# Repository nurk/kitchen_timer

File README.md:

### *Disclaimer*
*I am not a microcontroller developer nor am I a C-plusplus developer.  I am also definitively not a hardware designer.*

# Kitchen timer

A long time ago my lovely sister gave me a kitchen timer which would beep once when there are 10 minutes left and twice when there are 5 minutes left.  Unfortunately time got the better of the timer and it broke but I got hooked on those features.

I have been unable to find a replacement but after dabbling with some [circuits](https://github.com/nurk/8-bit-cpu) a bit I thought I might be able to make my own.

This repository contains the version(s) that I deem worthy of the internet.

You will find a software and hardware folder with each containing the respective versions.

The hardware folder contains a KiCad project where the symbols and footprints used have been added to a local library.  You will also find a pdf of the [schematic](https://github.com/nurk/kitchen_timer/blob/ce0c0dc44edd9d53a935f777b976885855d0056c/hardware/kitchen_timer_6.3/schematic.pdf), a screenshot of the [pcb](https://github.com/nurk/kitchen_timer/blob/ce0c0dc44edd9d53a935f777b976885855d0056c/hardware/kitchen_timer_6.3/pcb.png) and a screenshot of the [3D rendering](https://github.com/nurk/kitchen_timer/blob/ce0c0dc44edd9d53a935f777b976885855d0056c/hardware/kitchen_timer_6.3/3D.png).

The software folder contains an arduino ide project with the, well, software.

## User guide
I am not going to explain how to use a kitchen timer.  If the main function of the 4 buttons does not speak for themselves I did really bad.  I am only going to explain the extra features.

### Timer / C°
This switch toggles the display to show the timer and the measured temperature.

### Loud / Quiet
I bought cheap buzzers on amazon and they all seem a bit different.  Some are quiet and some are loud.  Because I was tired of changing the inline resistor for the buzzer I added a toggle to switch between two values.  One is louder, the other is quieter.

### Reset long press
Because you can fully turn off this device a way was needed to set the time for when you turn on the device.  The chance of you needing a timer of 0 minutes and 0 seconds is very slim.

After setting a time you can long press the **Reset** button until you hear a second beep and the set time will be stored.  When cycling the power the stored time will be loaded.

### Start/Stop long press
When you long press the **Start/Stop** button the letter `A` will appear and you will have entered the setup menu.  After releasing the **Start/Stop** button you will see `A5. 0`.  Clicking the **Start/Stop** button will cycle through the menu items:  
| Displayed        | Meaning         |
| :--------------: | :-------------: |
| `A5. 0`          | 5 minute alarm  |
| `A10.0`          | 10 minute alarm |
| `A15.0`          | 15 minute alarm |
| `A20.0`          | 20 minute alarm |
| `C 0.0`          | Temperature offset<sup>*</sup> |

<sup>*</sup> This was added in version 6.4.  It is a `C` because I cannot make a `T` with a 7-segment display.

For the alarms, the value after the `.` is the number of beeps that will sound when there are 'x' minutes left.  You can use the **Minutes** button to increase the number of beeps and the **Seconds** button to decrease the number of beeps.

To exit the setup menu just click the **Reset** button.

## Miscellaneous
Some component sizes might seem big for some.  Especially resistors and capacitors of size 0805.  Keep in mind I am hand soldering this and I am becoming an old fart with bad eyesight.

The microcontroller is an ATmega4808 which has way more flash storage than is needed.  I still chose this one because it is what I have and I am not going to buy a new variant for each project I do.

The battery charge controller I chose only charges at 500mA.  So you will need a battery with at least this capacity (or you have to change the resistor on the programming pin).  I have a 2000mA battery connected and I takes a fair while to charge.

**This is not a cost effective way to get a kitchen timer.  If you need one you are better of going to the store and buying one.**

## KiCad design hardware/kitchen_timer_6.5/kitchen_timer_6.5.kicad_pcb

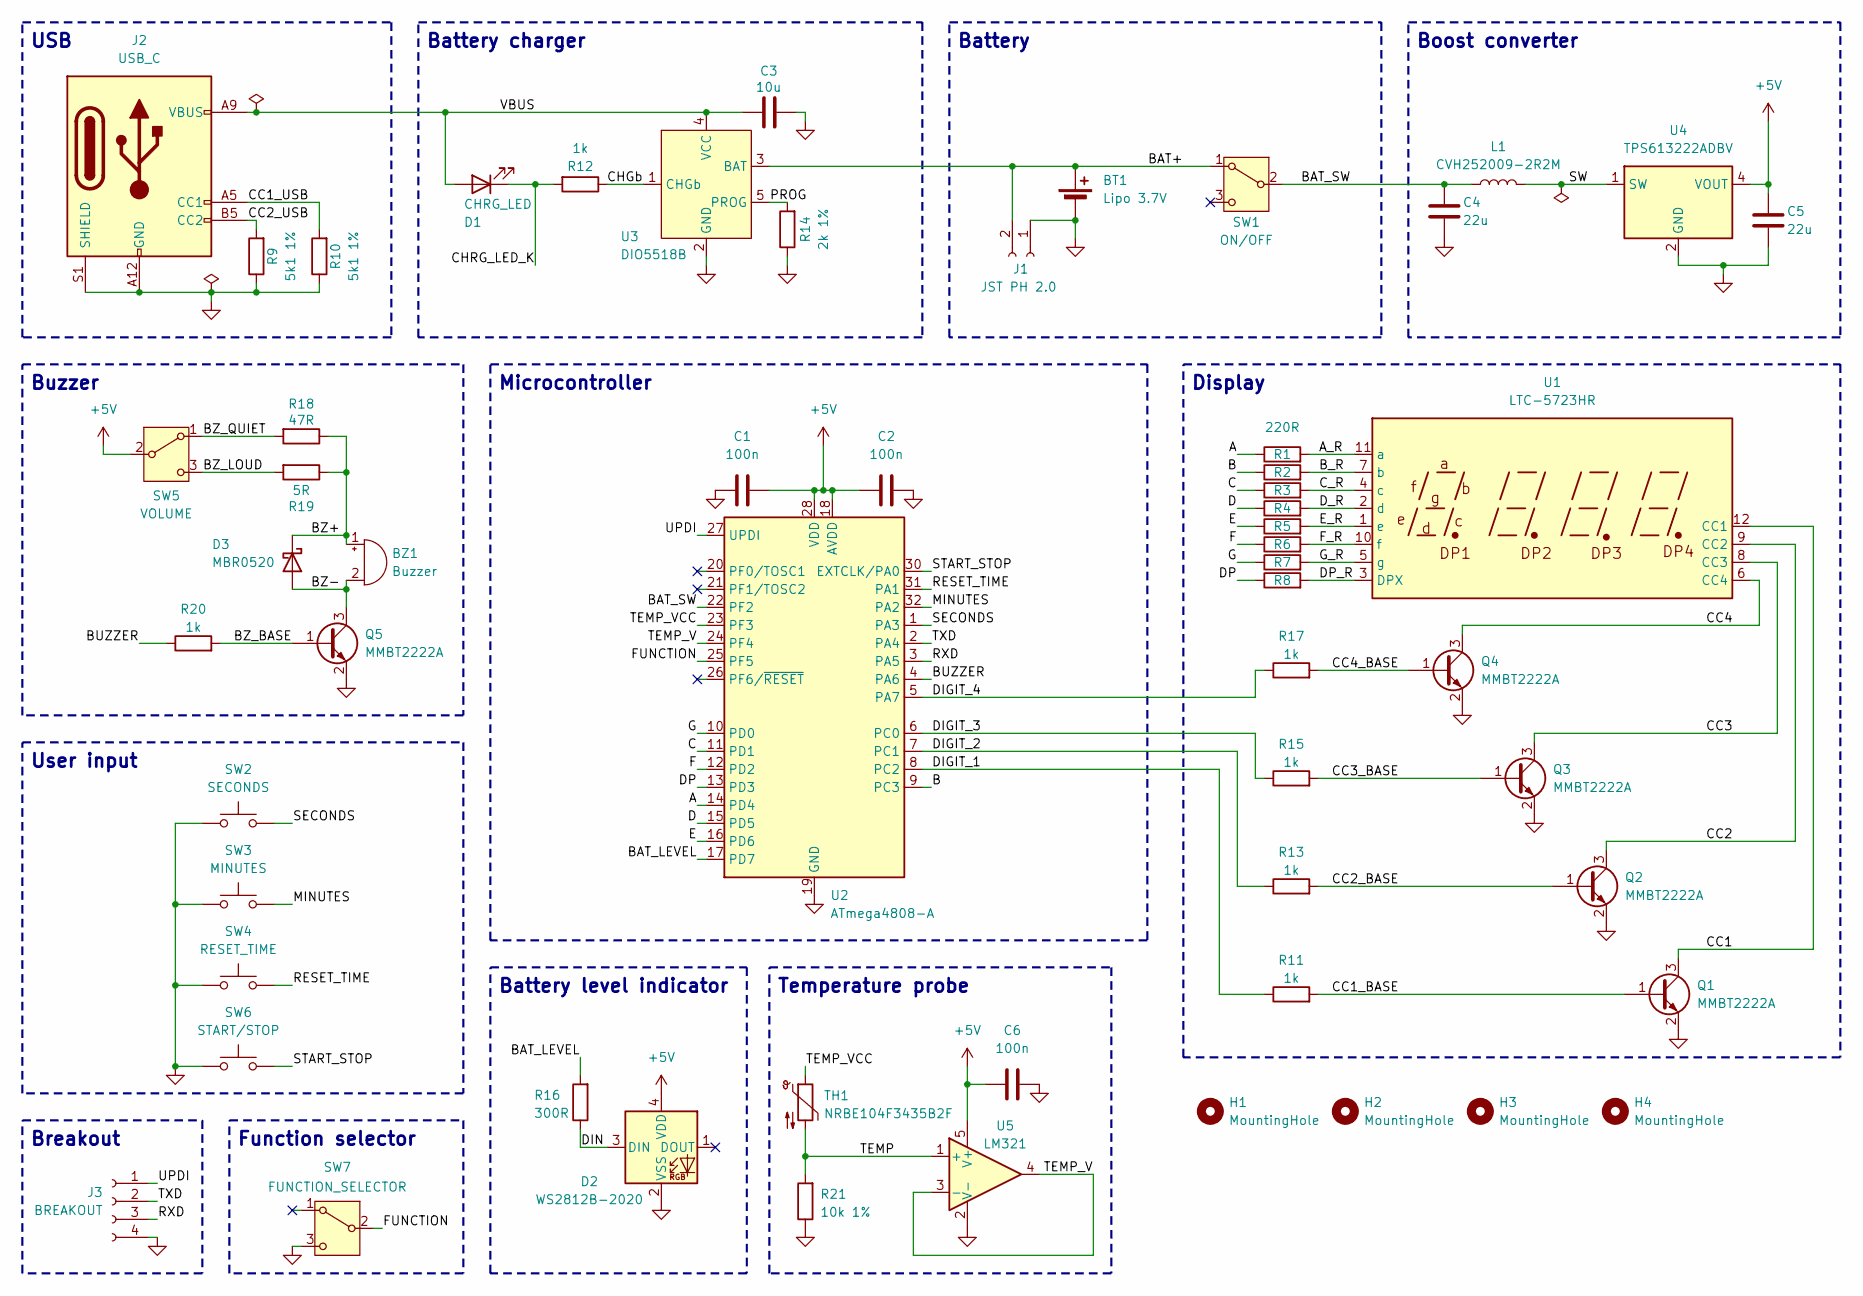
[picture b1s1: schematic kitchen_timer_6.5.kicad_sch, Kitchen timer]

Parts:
BT1: Lipo 3.7V
BZ1: Buzzer; MagneticBuzzer_ProSignal_ABT-410-RC
C1, C2, C6: 100n; C_0805_2012Metric_Pad1.18x1.45mm_HandSolder
C3: 10u; C_0805_2012Metric_Pad1.18x1.45mm_HandSolder
C4, C5: 22u; C_0805_2012Metric_Pad1.18x1.45mm_HandSolder
D1: CHRG_LED; D_0805_2012Metric_Pad1.15x1.40mm_HandSolder
D2: WS2812B-2020; LED_WS2812B-2020_2.0x2.0mm
D3: MBR0520; D_SOD-123
H1, H2, H3, H4: MountingHole; MountingHole_3.2mm_M3
J1: JST PH 2.0; JST_PH_S2B-PH-K_1x02_P2.00mm_Horizontal
J2: USB_C; USB_C_Receptacle_GCT_USB4125-xx-x-0190_6P_TopMnt_Horizontal
J3: BREAKOUT; PinSocket_1x04_P2.54mm_Vertical
L1: CVH252009-2R2M; L_1008_2520Metric_Pad1.43x2.20mm_HandSolder
Q1, Q2, Q3, Q4, Q5: MMBT2222A; SOT-23-3
R1, R2, R3, R4, R5, R6, R7, R8: 220R; R_0805_2012Metric_Pad1.20x1.40mm_HandSolder
R9, R10: 5k1 1%; R_0805_2012Metric_Pad1.20x1.40mm_HandSolder
R11, R12, R13, R15, R17, R20: 1k; R_0805_2012Metric_Pad1.20x1.40mm_HandSolder
R14: 2k 1%; R_0805_2012Metric_Pad1.20x1.40mm_HandSolder
R16: 300R; R_0805_2012Metric_Pad1.20x1.40mm_HandSolder
R18: 47R; R_0805_2012Metric_Pad1.20x1.40mm_HandSolder
R19: 5R; R_0805_2012Metric_Pad1.20x1.40mm_HandSolder
R21: 10k 1%; R_0805_2012Metric_Pad1.20x1.40mm_HandSolder
SW1: ON/OFF; SW_Slide_SPDT_MINI
SW2: SECONDS; SW_PUSH_6mm
SW3: MINUTES; SW_PUSH_6mm
SW4: RESET_TIME; SW_PUSH_6mm
SW5: VOLUME; SW_Slide_SPDT_MINI
SW6: START/STOP; SW_PUSH_6mm
SW7: FUNCTION_SELECTOR; SW_Slide_SPDT_MINI
TH1: NRBE104F3435B2F; PinSocket_1x02_P2.54mm_Vertical
U1: LTC-5723HR; CA56-12EWA
U2: ATmega4808-A; TQFP-32_7x7mm_P0.8mm
U3: DIO5518B; SOT-23-5
U4: TPS613222ADBV; SOT-23-5
U5: LM321; SOT-23-5

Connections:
+5V: C1.1, C2.2, C5.1, C6.2, D2.4 (VDD), SW5.2 (B), U2.18 (AVDD), U2.28 (VDD), U4.4 (VOUT), U5.5 (V+)
/A: R1.1, U2.14 (PD4)
/A_R: R1.2, U1.11 (a)
/B: R2.1, U2.9 (PC3)
/BAT+: BT1.1 (+), J1.2, SW1.1 (A), U3.3 (BAT)
/BAT_LEVEL: R16.2, U2.17 (PD7)
/BAT_SW: C4.1, L1.1, SW1.2 (B), U2.22 (PF2)
/BUZZER: R20.1, U2.4 (PA6)
/BZ+: BZ1.1 (+), D3.1 (K), R18.1, R19.1
/BZ-: BZ1.2 (-), D3.2 (A), Q5.3 (C)
/BZ_BASE: Q5.1 (B), R20.2
/BZ_LOUD: R19.2, SW5.3 (C)
/BZ_QUIET: R18.2, SW5.1 (A)
/B_R: R2.2, U1.7 (b)
/C: R3.1, U2.11 (PD1)
/CC1: Q1.3 (C), U1.12 (CC1)
/CC1_BASE: Q1.1 (B), R11.2
/CC1_USB: J2.A5 (CC1), R10.2
/CC2: Q2.3 (C), U1.9 (CC2)
/CC2_BASE: Q2.1 (B), R13.2
/CC2_USB: J2.B5 (CC2), R9.2
/CC3: Q3.3 (C), U1.8 (CC3)
/CC3_BASE: Q3.1 (B), R15.2
/CC4: Q4.3 (C), U1.6 (CC4)
/CC4_BASE: Q4.1 (B), R17.2
/CHGb: R12.1, U3.1 (CHGb)
/CHRG_LED_K: D1.1 (K), R12.2
/C_R: R3.2, U1.4 (c)
/D: R4.1, U2.15 (PD5)
/DIGIT_1: R11.1, U2.8 (PC2)
/DIGIT_2: R13.1, U2.7 (PC1)
/DIGIT_3: R15.1, U2.6 (PC0)
/DIGIT_4: R17.1, U2.5 (PA7)
/DIN: D2.3 (DIN), R16.1
/DP: R8.1, U2.13 (PD3)
/DP_R: R8.2, U1.3 (DPX)
/D_R: R4.2, U1.2 (d)
/E: R5.1, U2.16 (PD6)
/E_R: R5.2, U1.1 (e)
/F: R6.1, U2.12 (PD2)
/FUNCTION: SW7.2 (B), U2.25 (PF5)
/F_R: R6.2, U1.10 (f)
/G: R7.1, U2.10 (PD0)
/G_R: R7.2, U1.5 (g)
/MINUTES: SW3.2, U2.32 (PA2)
/PROG: R14.2, U3.5 (PROG)
/RESET_TIME: SW4.2, U2.31 (PA1)
/RXD: J3.3, U2.3 (PA5)
/SECONDS: SW2.2, U2.1 (PA3)
/START_STOP: SW6.2, U2.30 (EXTCLK/PA0)
/SW: L1.2, U4.1 (SW)
/TEMP: R21.2, TH1.2, U5.1 (+)
/TEMP_V: U2.24 (PF4), U5.3 (-), U5.4
/TEMP_VCC: TH1.1, U2.23 (PF3)
/TXD: J3.2, U2.2 (PA4)
/UPDI: J3.1, U2.27 (UPDI)
/VBUS: C3.1, D1.2 (A), J2.A9 (VBUS), J2.B9 (VBUS), U3.4 (VCC)
GND: BT1.2 (-), C1.2, C2.1, C3.2, C4.2, C5.2, C6.1, D2.2 (VSS), J1.1, J2.A12 (GND), J2.B12 (GND), J2.S1 (SHIELD), J3.4, Q1.2 (E), Q2.2 (E), Q3.2 (E), Q4.2 (E), Q5.2 (E), R9.1, R10.1, R14.1, R21.1, SW2.1, SW3.1, SW4.1, SW6.1, SW7.3 (C), U2.19 (GND), U2.29 (GND), U3.2 (GND), U4.2 (GND), U5.2 (V-)

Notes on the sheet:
Temperature probe
Battery
Display
Battery level indicator
USB
Function selector
Boost converter
User input
Microcontroller
Buzzer
Breakout
Battery charger

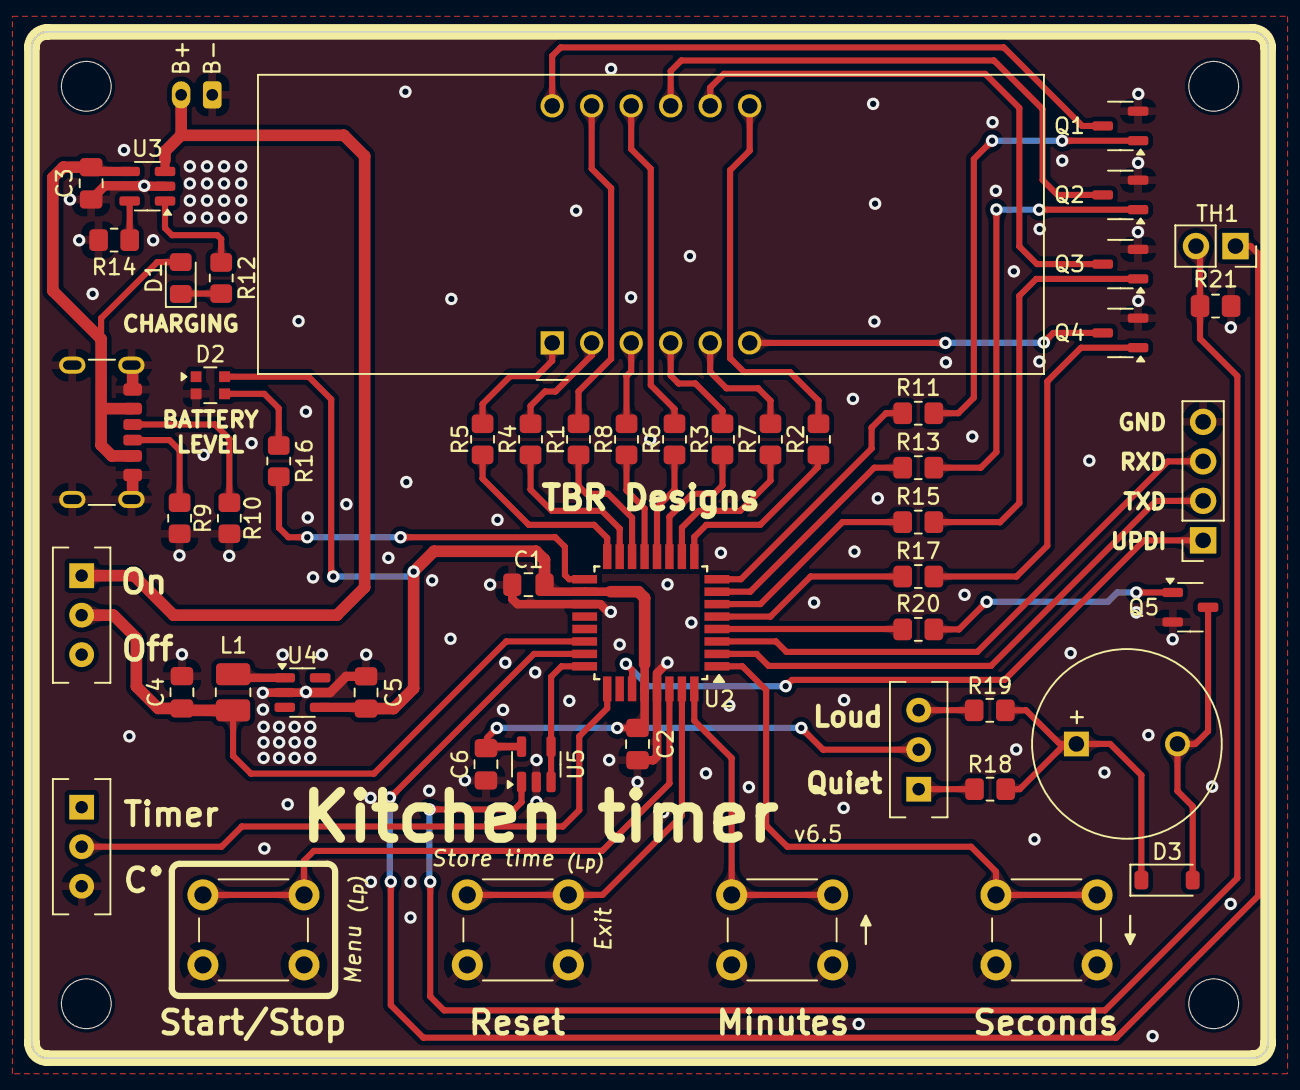
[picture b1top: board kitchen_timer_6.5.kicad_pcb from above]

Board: 2 copper layers, 79.5 x 66.0 mm, 57 parts (1 on the bottom side), 58 nets.

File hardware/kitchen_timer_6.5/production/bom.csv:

Designator,Footprint,Quantity,Value,LCSC Part #
BZ1,MagneticBuzzer_ProSignal_ABT-410-RC,1,Buzzer,
"C1, C2, C6",0805,3,100n,
C3,0805,1,10u,
"C4, C5",0805,2,22u,
D1,0805,1,CHRG_LED,
D2,LED_WS2812B-2020_2.0x2.0mm,1,WS2812B-2020,
D3,D_SOD-123,1,MBR0520,
J1,JST_PH_S2B-PH-K_1x02_P2.00mm_Horizontal,1,JST PH 2.0,
J2,USB_C_Receptacle_GCT_USB4125-xx-x-0190_6P_TopMnt_Horizontal,1,USB_C,
J3,PinSocket_1x04_P2.54mm_Vertical,1,BREAKOUT,
L1,1008,1,CVH252009-2R2M,
"Q1, Q2, Q3, Q4, Q5",SOT-23-3,5,MMBT2222A,
"R1, R2, R3, R4, R5, R6, R7, R8",0805,8,220R,
"R10, R9",0805,2,5k1 1%,
"R11, R12, R13, R15, R17, R20",0805,6,1k,
R14,0805,1,2k 1%,
R16,0805,1,300R,
R18,0805,1,47R,
R19,0805,1,5R,
R21,0805,1,10k 1%,
SW1,SW_Slide_SPDT_MINI,1,ON/OFF,
SW2,SW_PUSH_6mm,1,SECONDS,
SW3,SW_PUSH_6mm,1,MINUTES,
SW4,SW_PUSH_6mm,1,RESET_TIME,
SW5,SW_Slide_SPDT_MINI,1,VOLUME,
SW6,SW_PUSH_6mm,1,START/STOP,
SW7,SW_Slide_SPDT_MINI,1,FUNCTION_SELECTOR,
TH1,PinSocket_1x02_P2.54mm_Vertical,1,NRBE104F3435B2F,
U1,CA56-12EWA,1,LTC-5723HR,
U2,TQFP-32_7x7mm_P0.8mm,1,ATmega4808-A,
U3,SOT-23-5,1,DIO5518B,
U4,SOT-23-5,1,TPS613222ADBV,
U5,SOT-23-5,1,LM321,

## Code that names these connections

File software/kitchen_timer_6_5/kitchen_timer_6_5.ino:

/**
  SW: 6.4
  HW: 6.4

  ATmega4808
  Internal 16 MHz
  EEPROM retained
  32 pin standard
  Reset pin GPIO
  Serial UPDI
**/

#define DEBUG false
#define Serial \
  if (DEBUG) Serial

#include "HystFilter.h"
#include <JC_Button.h>
#include <EEPROM.h>
#include <Adafruit_NeoPixel.h>

#define USE_TIMER_0 true
#define TIMER_INTERVAL_MS 1000L
#include <megaAVR_TimerInterrupt.h>

#define A_SEGMENT PIN_PD4
#define B_SEGMENT PIN_PC3
#define C_SEGMENT PIN_PD1
#define D_SEGMENT PIN_PD5
#define E_SEGMENT PIN_PD6
#define F_SEGMENT PIN_PD2
#define G_SEGMENT PIN_PD0
#define DP_SEGMENT PIN_PD3

#define DIGIT_1 PIN_PC2
#define DIGIT_2 PIN_PC1
#define DIGIT_3 PIN_PC0
#define DIGIT_4 PIN_PA7

#define START_STOP PIN_PA0
#define TIME_RESET PIN_PA1
#define MINUTES PIN_PA2
#define SECONDS PIN_PA3

#define BUZZER PIN_PA6

#define BATTERY_LEVEL_PIN PIN_PF2
#define BATTERY_LEVEL_LED_PIN PIN_PD7

#define TEMP_V PIN_PF4
#define TEMP_VCC PIN_PF3
#define FUNCTION PIN_PF5

const int segments[] = { A_SEGMENT, B_SEGMENT, C_SEGMENT, D_SEGMENT, E_SEGMENT, F_SEGMENT, G_SEGMENT, DP_SEGMENT };
const int digits[] = { DIGIT_1, DIGIT_2, DIGIT_3, DIGIT_4 };

// Dp G F E D C B A
const byte numbers[] = {
  0X3F,  // 0
  0X06,  // 1
  0X5B,  // 2
  0X4F,  // 3
  0X66,  // 4
  0X6D,  // 5
  0X7C,  // 6
  0X07,  // 7
  0X7F,  // 8
  0X6F   // 9
};
const byte blankDigit = 0X00;
const byte aDigit = 0X77;
const byte cDigit = 0X39;
const byte minusDigit = 0X40;

int currentDigit = 0;
unsigned long digitMillis = millis();

const Button startStopButton(START_STOP);
const Button timeResetButton(TIME_RESET);
const Button minutesButton(MINUTES);
const Button secondsButton(SECONDS);
boolean resetLongPressed = false;
// for state machine used by mintues and seconds button
// see https://github.com/JChristensen/JC_Button/blob/master/examples/UpDown/UpDown.ino
const unsigned long REPEAT_FIRST(500);
const unsigned long REPEAT_INCR(100);
unsigned long rpt(REPEAT_FIRST);
enum states_t { WAIT,
                MINUTES_UP,
                SECONDS_UP };
states_t STATE;

int seconds = 0;
int minutes = 0;
int previousSeconds = 0;
int previousMinutes = 0;
const int minutesAddress = 0;
const int secondsAddress = 2;
bool counting = false;
bool buzzing = false;
bool pauzed = false;

const int beepTone = 1800;

int bleepsToDo = 0;
unsigned long nextBleepTime = millis();

int bleepBlocksToDo = 0;
unsigned long nextBleepBlockTime = millis();

boolean setupMenu = false;
int menuItem = 0;
int alarm5MinutesBleeps = 0;
int alarm10MinutesBleeps = 0;
int alarm15MinutesBleeps = 0;
int alarm20MinutesBleeps = 0;
const int alarm5MinutesAddress = 4;
const int alarm10MinutesAddress = 6;
const int alarm15MinutesAddress = 8;
const int alarm20MinutesAddress = 10;

Adafruit_NeoPixel pixels(1, BATTERY_LEVEL_LED_PIN, NEO_GRB + NEO_KHZ800);
unsigned long nextBatteryLevelCheck = 0;

unsigned long nextFunctionCheck = millis();
boolean isTimerDisplayed = true;

unsigned long nextTemperatureCheck = millis();
int tempMostSignificant = 0;
int tempLeastSignificant = 0;
float tempOffset = 0.0;
const int tempOffsetAddress = 12;  // 4 bytes

void setup() {
  Serial.swap(1);
  Serial.begin(9600);
  pinMode(A_SEGMENT, OUTPUT);
  pinMode(B_SEGMENT, OUTPUT);
  pinMode(C_SEGMENT, OUTPUT);
  pinMode(D_SEGMENT, OUTPUT);
  pinMode(E_SEGMENT, OUTPUT);
  pinMode(F_SEGMENT, OUTPUT);
  pinMode(G_SEGMENT, OUTPUT);
  pinMode(DP_SEGMENT, OUTPUT);

  pinMode(DIGIT_1, OUTPUT);
  pinMode(DIGIT_2, OUTPUT);
  pinMode(DIGIT_3, OUTPUT);
  pinMode(DIGIT_4, OUTPUT);

  pinMode(BUZZER, OUTPUT);

  pinMode(FUNCTION, INPUT_PULLUP);
  pinMode(TEMP_VCC, OUTPUT);

  isTimerDisplayed = digitalRead(FUNCTION) == HIGH;

  startStopButton.begin();
  timeResetButton.begin();
  minutesButton.begin();
  secondsButton.begin();

  ITimer0.init();
  ITimer0.attachInterruptInterval(TIMER_INTERVAL_MS, timerHandler);

  loadEEPROM();

  pixels.begin();
  pixels.setBrightness(10);
  pixels.setPixelColor(0, pixels.Color(255, 255, 255));
  pixels.show();

  digitalWrite(TEMP_VCC, HIGH);
  convertThermistorReading(analogRead(TEMP_V));
  digitalWrite(TEMP_VCC, LOW);
}

void loop() {
  handleFunction();
  handleBatteryLevel();
  handleTemperature();
  multiplexDigits();
  handleButtons();
  handleBleeps();
}

void loadEEPROM() {
  EEPROM.get(secondsAddress, seconds);
  EEPROM.get(minutesAddress, minutes);
  EEPROM.get(alarm5MinutesAddress, alarm5MinutesBleeps);
  EEPROM.get(alarm10MinutesAddress, alarm10MinutesBleeps);
  EEPROM.get(alarm15MinutesAddress, alarm15MinutesBleeps);
  EEPROM.get(alarm20MinutesAddress, alarm20MinutesBleeps);
  EEPROM.get(tempOffsetAddress, tempOffset);

  seconds = min(59, max(0, seconds));
  minutes = min(99, max(0, minutes));
  previousSeconds = seconds;
  previousMinutes = minutes;

  alarm5MinutesBleeps = min(9, max(0, alarm5MinutesBleeps));
  alarm10MinutesBleeps = min(9, max(0, alarm10MinutesBleeps));
  alarm15MinutesBleeps = min(9, max(0, alarm15MinutesBleeps));
  alarm20MinutesBleeps = min(9, max(0, alarm20MinutesBleeps));

  tempOffset = fmin(9.9, fmax(-9.9, tempOffset));
}

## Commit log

2024-09-05 add schematic
2024-09-05 added images
2024-09-05 update git ignore
2024-09-05 readme
2024-09-05 readme edits
2024-09-05 Create LICENSE
2024-09-05 some code changed
2024-09-07 change to battery percentage
2024-09-07 add hysteresis for battery level
2024-09-07 fix readme
2024-09-24 version 6.4. PF0 cannot do analog read
2024-09-24 updated pcb.png
2024-09-24 new production file
2024-09-25 add temperature offset menu item
2024-09-25 readme for broken version
2024-09-29 extra capacitor
2024-10-04 actually order production files
2024-10-18 populated and programmed
2024-10-20 redid the schematic without reannotating. Hoping to me the usb -> battery charger -> boost converter more clear
2025-02-23 added opamp for temp sensing
2025-02-23 converted temp_gnd to temp_vcc and change temperature reading logic
2026-05-16 Add GNU Affero General Public License v3
